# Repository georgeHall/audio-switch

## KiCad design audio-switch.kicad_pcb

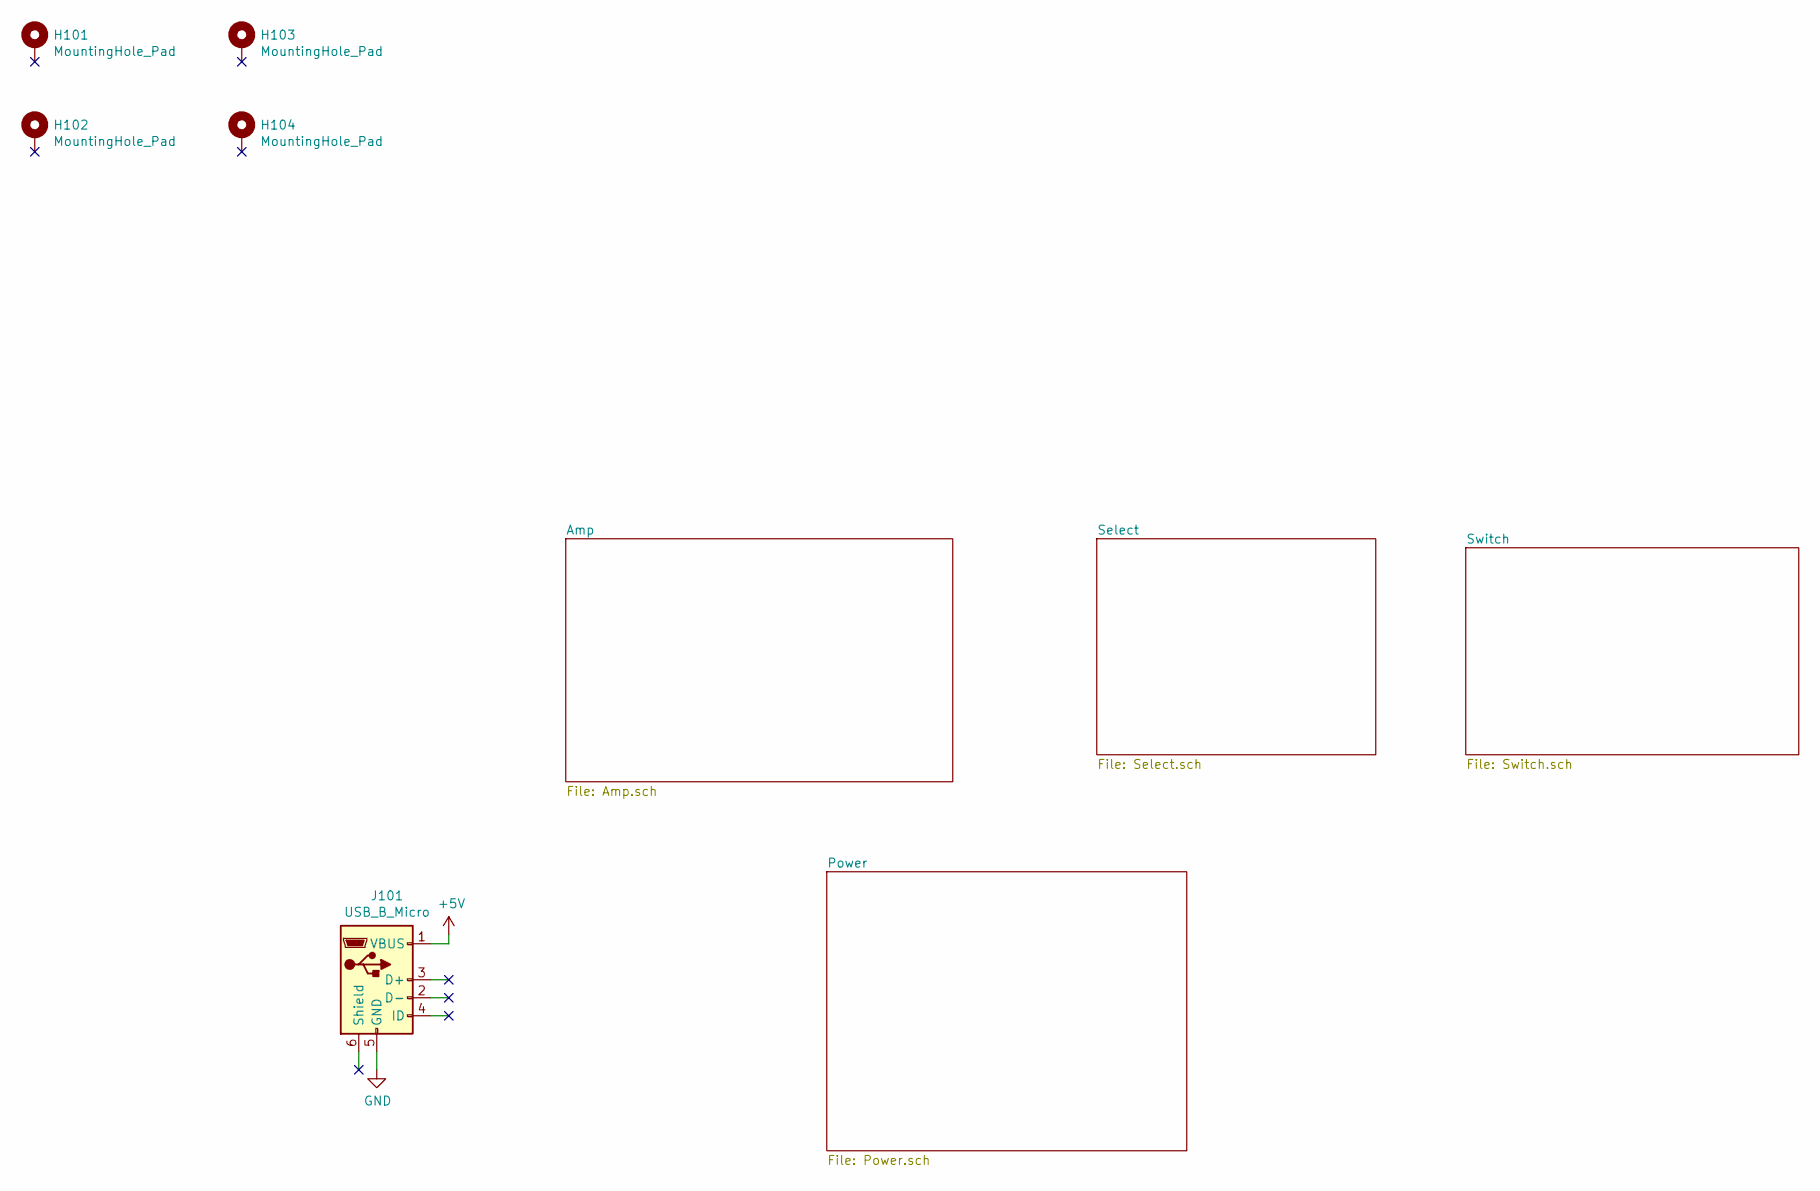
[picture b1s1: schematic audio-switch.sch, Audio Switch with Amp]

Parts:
H101, H102, H103, H104: MountingHole_Pad; MountingHole_2.2mm_M2
J101: USB_B_Micro; USB_Micro-B_Amphenol_10118194_Horizontal

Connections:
+5V: J101.1 (VBUS); also elsewhere on the board
GND: J101.5 (GND); also elsewhere on the board

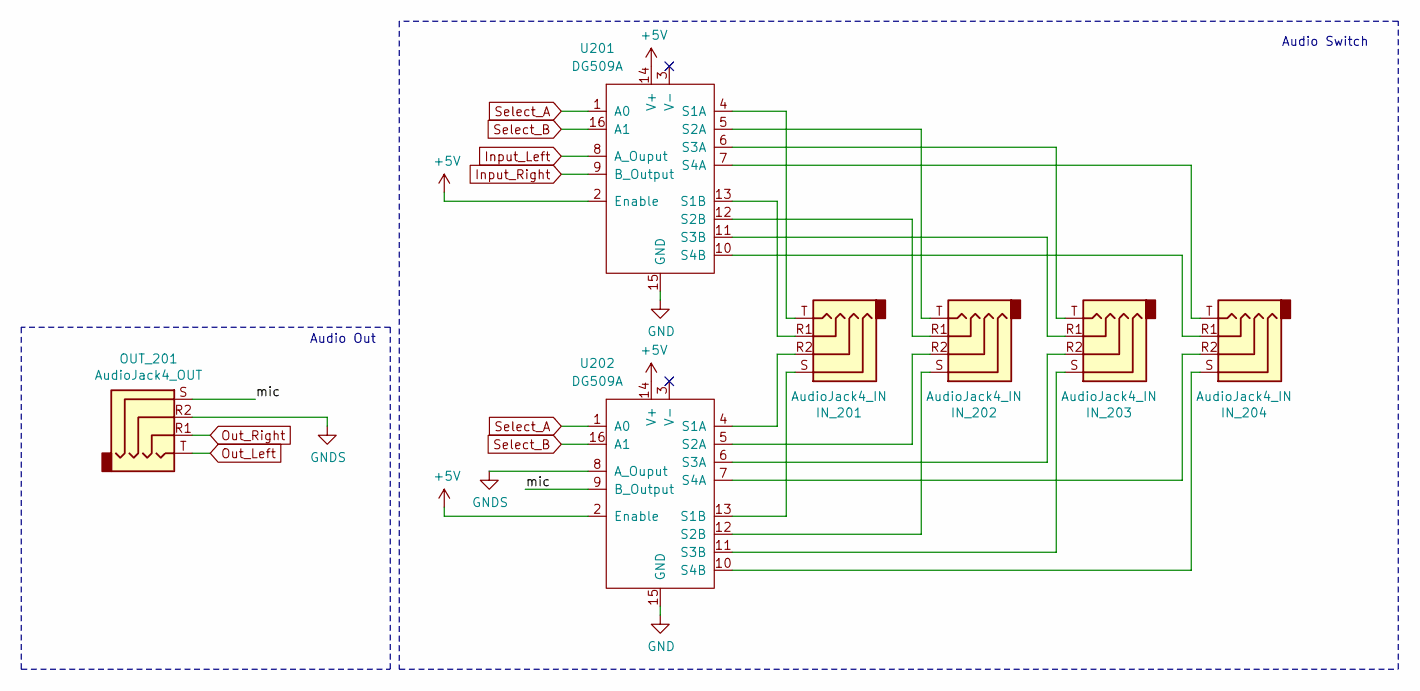
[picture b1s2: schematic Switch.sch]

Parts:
IN_201, IN_202, IN_203, IN_204: AudioJack4_IN
OUT_201: AudioJack4_OUT
U201, U202: DG509A; DIP-16_W7.62mm

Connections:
+5V: U201.2 (Enable), U201.14 (V+), U202.2 (Enable), U202.14 (V+); also elsewhere on the board
/Switch/mic: OUT_201.S, U202.9 (B_Output)
GND: U201.15 (GND), U202.15 (GND); also elsewhere on the board
GNDS: OUT_201.R2, U202.8 (A_Ouput)
Input_Left: U201.8 (A_Ouput); also elsewhere on the board
Input_Right: U201.9 (B_Output); also elsewhere on the board
unnamed: IN_201.R1, U201.13 (S1B)
unnamed: IN_201.R2, U202.4 (S1A)
unnamed: IN_201.S, U202.13 (S1B)
unnamed: IN_201.T, U201.4 (S1A)
unnamed: IN_202.R1, U201.12 (S2B)
unnamed: IN_202.R2, U202.5 (S2A)
unnamed: IN_202.S, U202.12 (S2B)
unnamed: IN_202.T, U201.5 (S2A)
unnamed: IN_203.R1, U201.11 (S3B)
unnamed: IN_203.R2, U202.6 (S3A)
unnamed: IN_203.S, U202.11 (S3B)
unnamed: IN_203.T, U201.6 (S3A)
unnamed: IN_204.R1, U201.10 (S4B)
unnamed: IN_204.R2, U202.7 (S4A)
unnamed: IN_204.S, U202.10 (S4B)
unnamed: IN_204.T, U201.7 (S4A)
Select_A: U201.1 (A0), U202.1 (A0); also elsewhere on the board
Select_B: U201.16 (A1), U202.16 (A1); also elsewhere on the board

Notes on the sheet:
Audio Out
Audio Switch

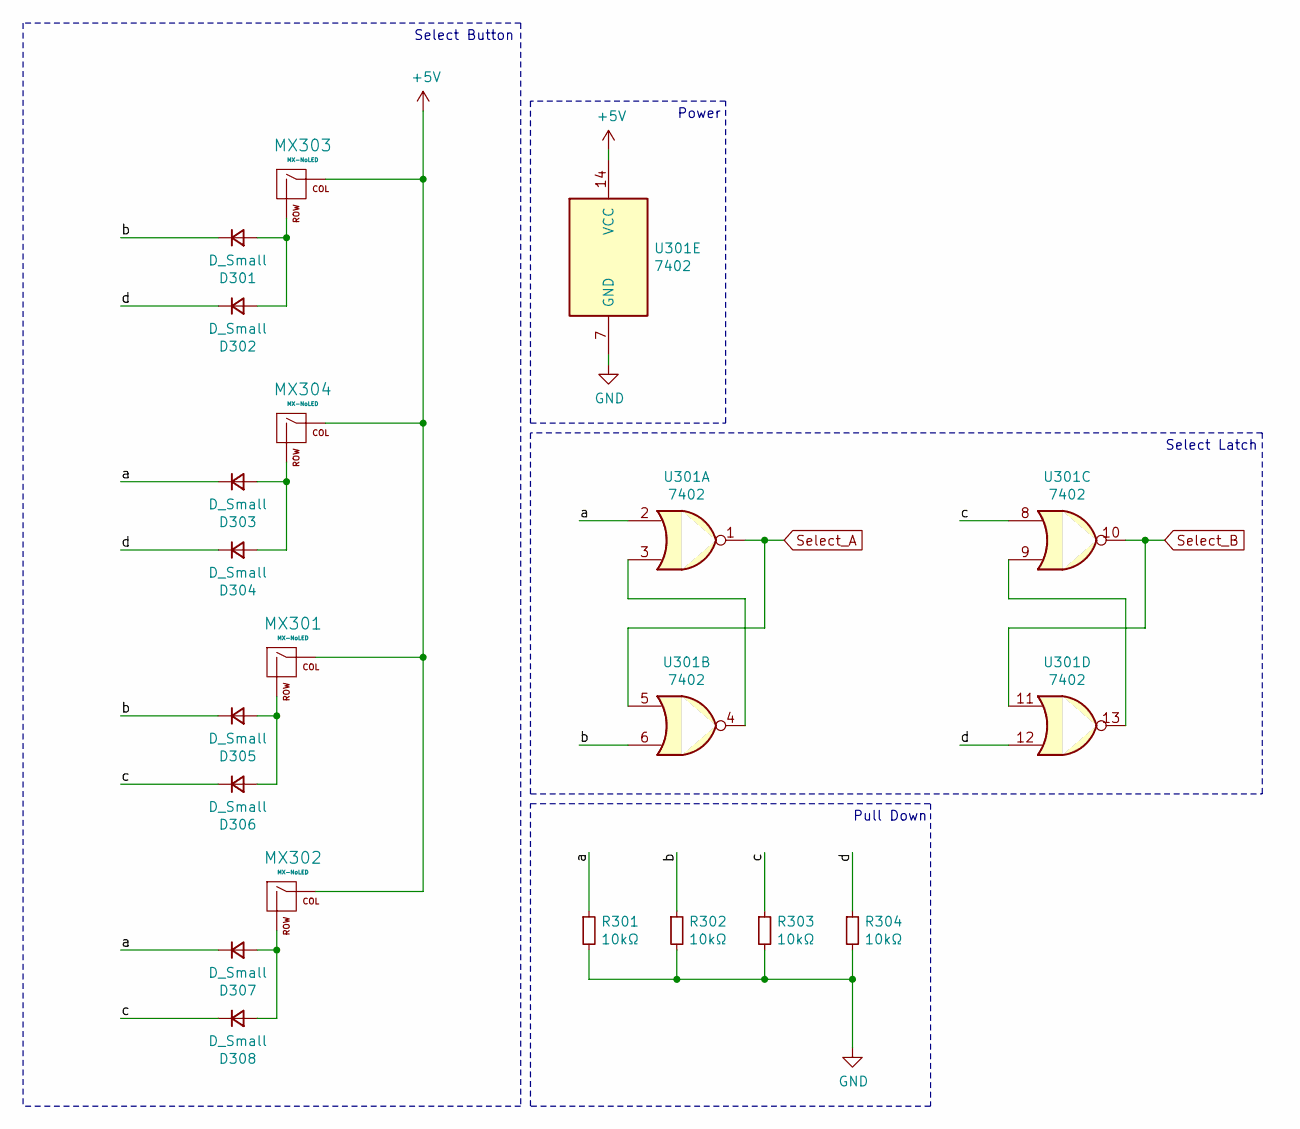
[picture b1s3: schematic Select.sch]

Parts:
D301, D302, D303, D304, D305, D306, D307, D308: D_Small; D_0805_2012Metric_Pad1.15x1.40mm_HandSolder
MX301, MX302, MX303, MX304: MX-NoLED; MXOnly-1U-NoLED
R301, R302, R303, R304: 10kΩ; R_0805_2012Metric_Pad1.20x1.40mm_HandSolder
U301: 7402; DIP-14_W7.62mm

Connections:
+5V: MX301.1 (COL), MX302.1 (COL), MX303.1 (COL), MX304.1 (COL), U301.14 (VCC); also elsewhere on the board
/Select/a: D303.1 (K), D307.1 (K), R301.1, U301.2
/Select/b: D301.1 (K), D305.1 (K), R302.1, U301.6
/Select/c: D306.1 (K), D308.1 (K), R303.1, U301.8
/Select/d: D302.1 (K), D304.1 (K), R304.1, U301.12
GND: R301.2, R302.2, R303.2, R304.2, U301.7 (GND); also elsewhere on the board
unnamed: D301.2 (A), D302.2 (A), MX303.2 (ROW)
unnamed: D303.2 (A), D304.2 (A), MX304.2 (ROW)
unnamed: D305.2 (A), D306.2 (A), MX301.2 (ROW)
unnamed: D307.2 (A), D308.2 (A), MX302.2 (ROW)
unnamed: U301.3, U301.4
unnamed: U301.9, U301.13
Select_A: U301.1, U301.5; also elsewhere on the board
Select_B: U301.10, U301.11; also elsewhere on the board

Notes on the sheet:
Select Button
Power
Select Latch
Pull Down

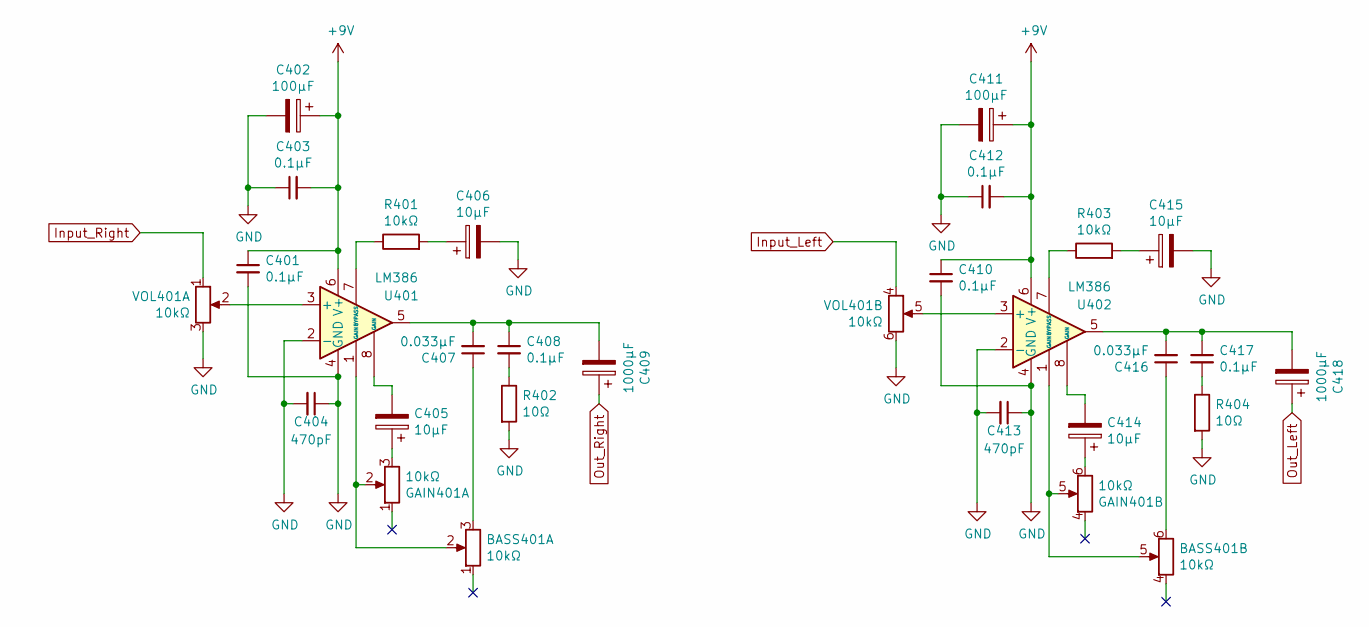
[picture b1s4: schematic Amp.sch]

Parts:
BASS401: 10kΩ; dual_pot_jaycar
C401, C403, C408, C410, C412, C417: 0.1µF; C_0805_2012Metric_Pad1.18x1.45mm_HandSolder
C402, C411: 100µF; CP_EIA-2012-15_AVX-P_Pad1.30x1.05mm_HandSolder
C404, C413: 470pF; C_0805_2012Metric_Pad1.18x1.45mm_HandSolder
C405, C406, C414, C415: 10µF; CP_EIA-2012-15_AVX-P_Pad1.30x1.05mm_HandSolder
C407, C416: 0.033µF; C_0805_2012Metric_Pad1.18x1.45mm_HandSolder
C409, C418: 1000µF; CP_Radial_D12.5mm_P5.00mm
GAIN401: 10kΩ; dual_pot_jaycar
R401, R403: 10kΩ; R_0805_2012Metric_Pad1.20x1.40mm_HandSolder
R402, R404: 10Ω; R_0805_2012Metric_Pad1.20x1.40mm_HandSolder
U401, U402: LM386; DIP-8_W7.62mm
VOL401: 10kΩ; dual_pot_jaycar

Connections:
+9V: C401.1, C402.1, C403.2, C410.1, C411.1, C412.2, U401.6 (V+), U402.6 (V+); also elsewhere on the board
GND: C401.2, C402.2, C403.1, C404.1, C404.2, C406.2, C410.2, C411.2, C412.1, C413.1, C413.2, C415.2, R402.2, R404.2, U401.2 (-), U401.4 (GND), U402.2 (-), U402.4 (GND), VOL401.3, VOL401.6; also elsewhere on the board
Input_Left: VOL401.4; also elsewhere on the board
Input_Right: VOL401.1; also elsewhere on the board
unnamed: BASS401.2, GAIN401.2, U401.1 (GAIN)
unnamed: BASS401.3, C407.1
unnamed: BASS401.5, GAIN401.5, U402.1 (GAIN)
unnamed: BASS401.6, C416.1
unnamed: C405.1, GAIN401.3
unnamed: C405.2, U401.8 (GAIN)
unnamed: C406.1, R401.2
unnamed: C407.2, C408.1, C409.2, U401.5
unnamed: C408.2, R402.1
unnamed: C414.1, GAIN401.6
unnamed: C414.2, U402.8 (GAIN)
unnamed: C415.1, R403.2
unnamed: C416.2, C417.1, C418.2, U402.5
unnamed: C417.2, R404.1
unnamed: R401.1, U401.7 (BYPASS)
unnamed: R403.1, U402.7 (BYPASS)
unnamed: U401.3 (+), VOL401.2
unnamed: U402.3 (+), VOL401.5
Out_Right: C409.1

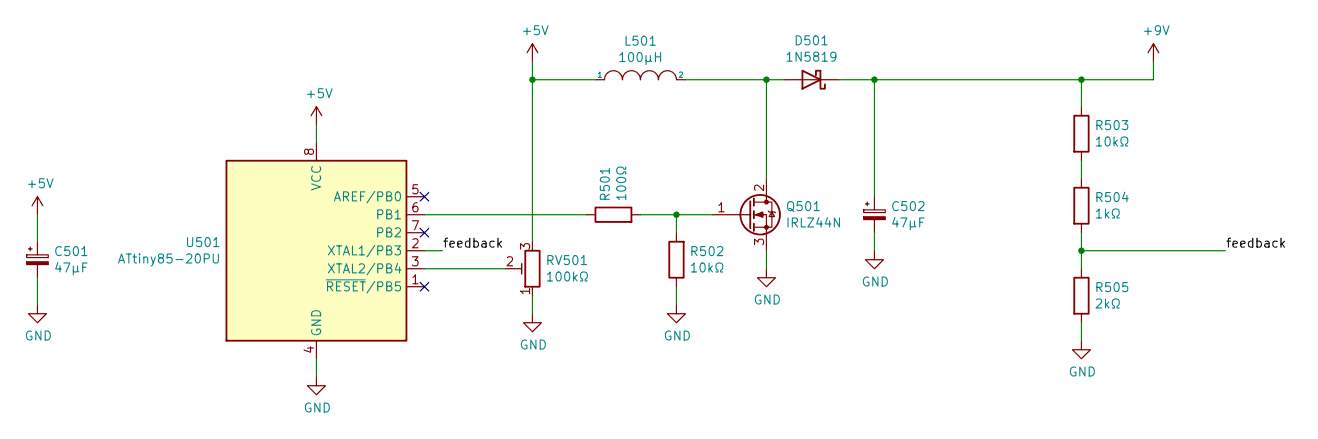
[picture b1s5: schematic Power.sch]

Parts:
C501, C502: 47µF; CP_EIA-2012-15_AVX-P_Pad1.30x1.05mm_HandSolder
D501: 1N5819; D_DO-41_SOD81_P7.62mm_Horizontal
L501: 100µH; L_Radial_D6.0mm_P4.00mm
Q501: IRLZ44N; TO-220-3_Vertical
R501: 100Ω; R_0805_2012Metric_Pad1.20x1.40mm_HandSolder
R502, R503: 10kΩ; R_0805_2012Metric_Pad1.20x1.40mm_HandSolder
R504: 1kΩ; R_0805_2012Metric_Pad1.20x1.40mm_HandSolder
R505: 2kΩ; R_0805_2012Metric_Pad1.20x1.40mm_HandSolder
RV501: 100kΩ; pot_jaycar
U501: ATtiny85-20PU; DIP-8_W7.62mm

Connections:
+5V: C501.1, L501.1, RV501.3, U501.8 (VCC); also elsewhere on the board
+9V: C502.1, D501.1 (K), R503.1; also elsewhere on the board
/Power/feedback: R504.2, R505.1, U501.2 (XTAL1/PB3)
GND: C501.2, C502.2, Q501.3 (S), R502.1, R505.2, RV501.1, U501.4 (GND); also elsewhere on the board
unnamed: D501.2 (A), L501.2, Q501.2 (D)
unnamed: Q501.1 (G), R501.2, R502.2
unnamed: R501.1, U501.6 (PB1)
unnamed: R503.2, R504.1
unnamed: RV501.2, U501.3 (XTAL2/PB4)

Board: 2 copper layers, 62 parts (0 on the bottom side), 41 nets, no tracks yet.

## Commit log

2021-07-23 Added Pico
2021-07-23 Setting up libs
2021-07-23 Rename dir and added libraries to pro
2021-07-23 Added switch matrix
2021-07-23 Wired switch and led matrix
2021-07-23 Schematic maybe is done.
2021-07-24 Added pico code
2021-07-24 Setup Pins
2021-07-24 Move pico
2021-07-26 Updated pico code and moved some stuff around
2021-07-26 Refactored pico
2021-07-26 More reusable
2021-07-29 Remove second switch case
2021-07-31 Update to use output class
2021-07-31 Change the voltage
2021-08-04 update the order
2021-08-08 Reorder commands
2021-08-10 Remove empty dir
2021-08-10 Added esp
2021-08-14 Edit pico
2021-08-14 Pass vars to functions
2021-08-14 Move function to file
2021-08-15 Remove pico
2021-08-15 Added loop for function
2021-08-31 Remove pico and use sr latch for input slection
2021-08-31 Remove esp32
2021-09-07 Added amps
2021-09-07 refactor
2021-09-12 Latch
2021-09-16 Temp
2021-10-03 Board designed.
2021-10-16 Clean up
2021-10-18 Update include power sections.
2021-10-25 Test
2021-10-25 Backup
